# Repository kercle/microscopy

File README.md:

# Microscope automation project

This is a small passion project of mine in which I implement a few automations to my Bresser Researcher Trino 40-1000x. A few design-goals are:

- Minimally intrusive in the sense that the changes to the microscope should be revertible as much as possible.
- The microscope should still be fully usable in the original (analogue) way.

## Gallery

A few composite images obtained by focus stacking:

| Daphnia | Spider mite | Unknown mite |
|---------|-------------|--------------------------|
|  |  |  |
| *Notes:* The sample was treated with bleach in order to immobilize organisms. Brownian motion was prevented by stabilizing the sample in Xanthan gum. | *Notes:* The sample was frozen to immobilize the specimen. It was taken from one of my house plants. | *Notes:* The sample was collected from the soil in one of my house plants. It was immobilized by freezing. Possibly of the order Mesostigmata. |

## Hardware

### Electronics

The control electronics is split between two controllers. The low-level control is handled by an ESP32 microcontroller, with the stepping motors being driven by TMC2208 stepper drivers.

The high-level control is handled by a Raspberry Pi 4, however the housing also allows for the installation of a Jetson Nano device instead of the Raspberry Pi.

The Raspberry Pi and ESP32 communicate over a serial connection (UART) using a custom protocol.

## Software

### User interface and backend

The user interface is a web application served by the Raspberry Pi. The frontend is built using Svelte, Tailwind CSS and DaisyUI. The backend is a Rust application using the Axum framework.

### Firmware

The ESP32 firmware is written in Rust using the `esp-idf` framework and embassy.

## Roadmap / Ideas for future work

- [x] Motorized z-axis with endstops for focusing
- [x] Web interface for controlling the microscope
- [x] Live view from camera with controls for exposure, gain, white balance, etc.
- [x] Z-stack acquisition
- [ ] Build custom focus knob which interacts with the microcontroller to allow for manual focusing when not using the web interface.
- [ ] Motorized stage for x/y movement
- [ ] Build custom stage knobs which interact with the microcontroller to allow for manual x/y
- [ ] Objective turret slot detection
- [ ] Substage illumination control
- [ ] Incident illumination

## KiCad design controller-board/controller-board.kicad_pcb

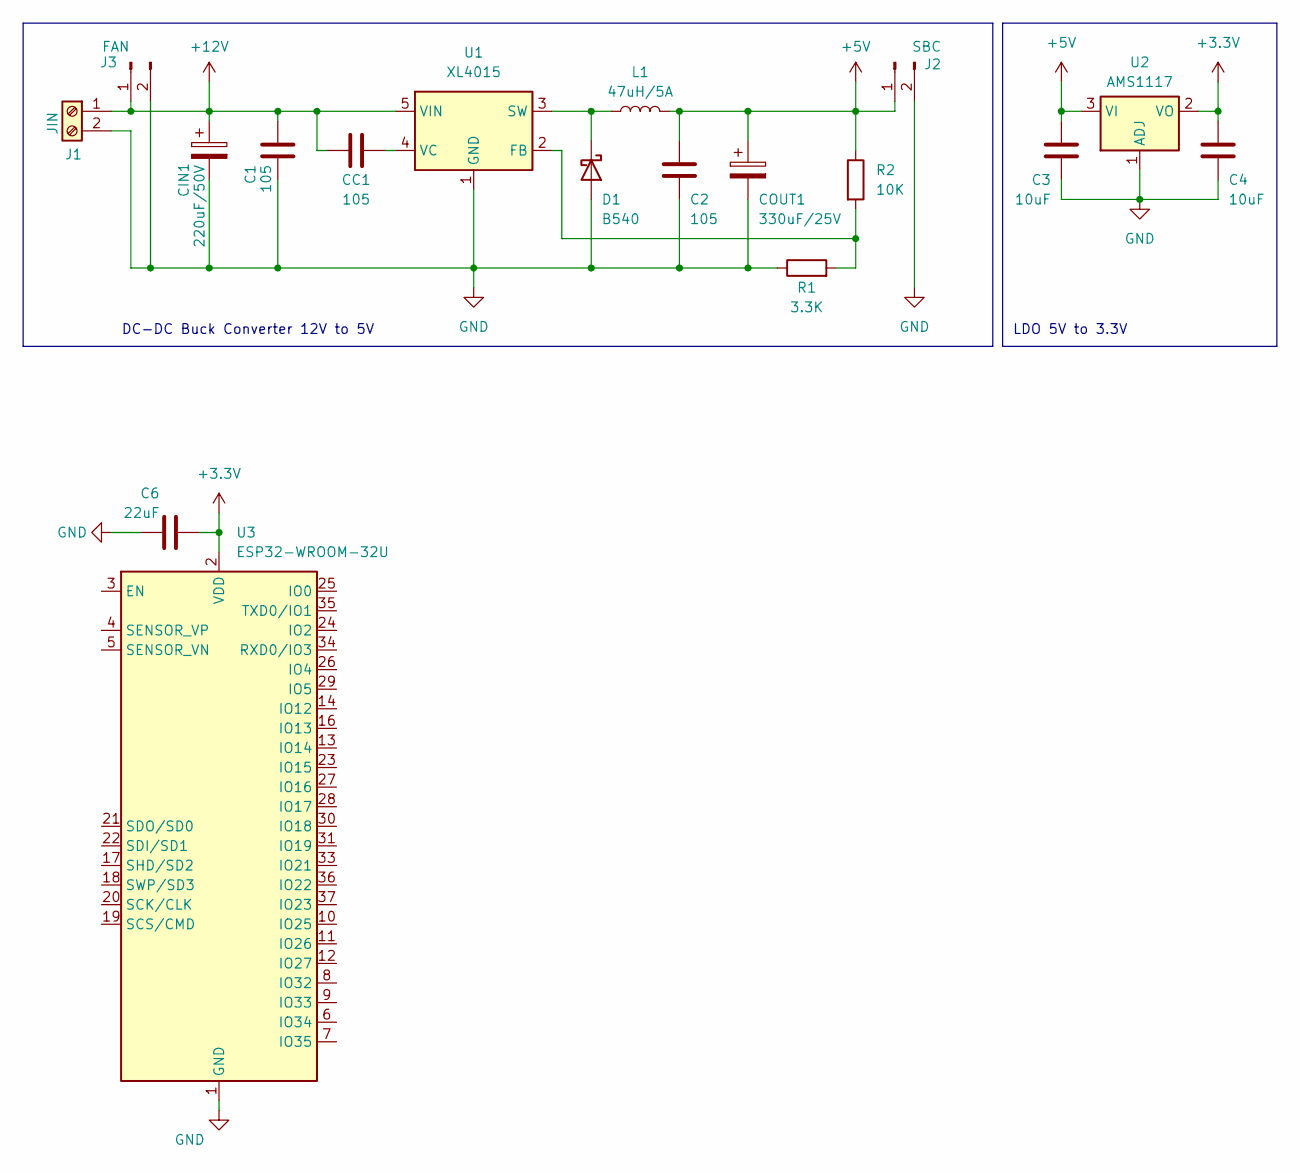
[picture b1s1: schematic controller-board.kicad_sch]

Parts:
C1, C2: 105; C_0805_2012Metric
C3, C4: 10uF; C_0805_2012Metric
C6: 22uF; C_0805_2012Metric
CC1: 105; C_0805_2012Metric
CIN1: 220uF/50V; CP_Elec_10x10; MFR# RVT1H221M1010 220UF 50V
COUT1: 330uF/25V; CP_Elec_10x10; MFR# RVT1H221M1010 220UF 50V
D1: B540; D_SMA
J1: JIN; TerminalBlock_Altech_AK300-2_P5.00mm
J2: SBC; JST_VH_B2P-VH-FB-B_1x02_P3.96mm_Vertical
J3: FAN; JST_VH_B2P-VH-FB-B_1x02_P3.96mm_Vertical
L1: 47uH/5A; L_Chilisin_BMRF00131360; MFR# YSPI1365-470M; JLCPCB# C497913
R1: 3.3K; R_0805_2012Metric
R2: 10K; R_0805_2012Metric
U1: XL4015; TO-263-5_TabPin3
U2: AMS1117; SOT-223-3_TabPin2
U3: ESP32-WROOM-32U

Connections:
+3.3V: C4.1, C6.2, U2.2 (VO), U3.2 (VDD)
+5V: C2.1, C3.1, COUT1.1, J2.1, L1.2, R2.1, U2.3 (VI)
+12V: C1.1, CC1.1, CIN1.1, J1.1, J3.1, U1.5 (VIN)
GND: C1.2, C2.2, C3.2, C4.2, C6.1, CIN1.2, COUT1.2, D1.2 (A), J1.2, J2.2, J3.2, R1.1, U1.1 (GND), U2.1 (ADJ), U3.1 (GND), U3.15 (GND), U3.38 (GND), U3.39 (GND)
unnamed: D1.1 (K), L1.1, U1.3 (SW)
unnamed: R1.2, R2.2, U1.2 (FB)
unnamed: CC1.2, U1.4 (VC)

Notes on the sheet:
DC-DC Buck Converter 12V to 5V
LDO 5V to 3.3V

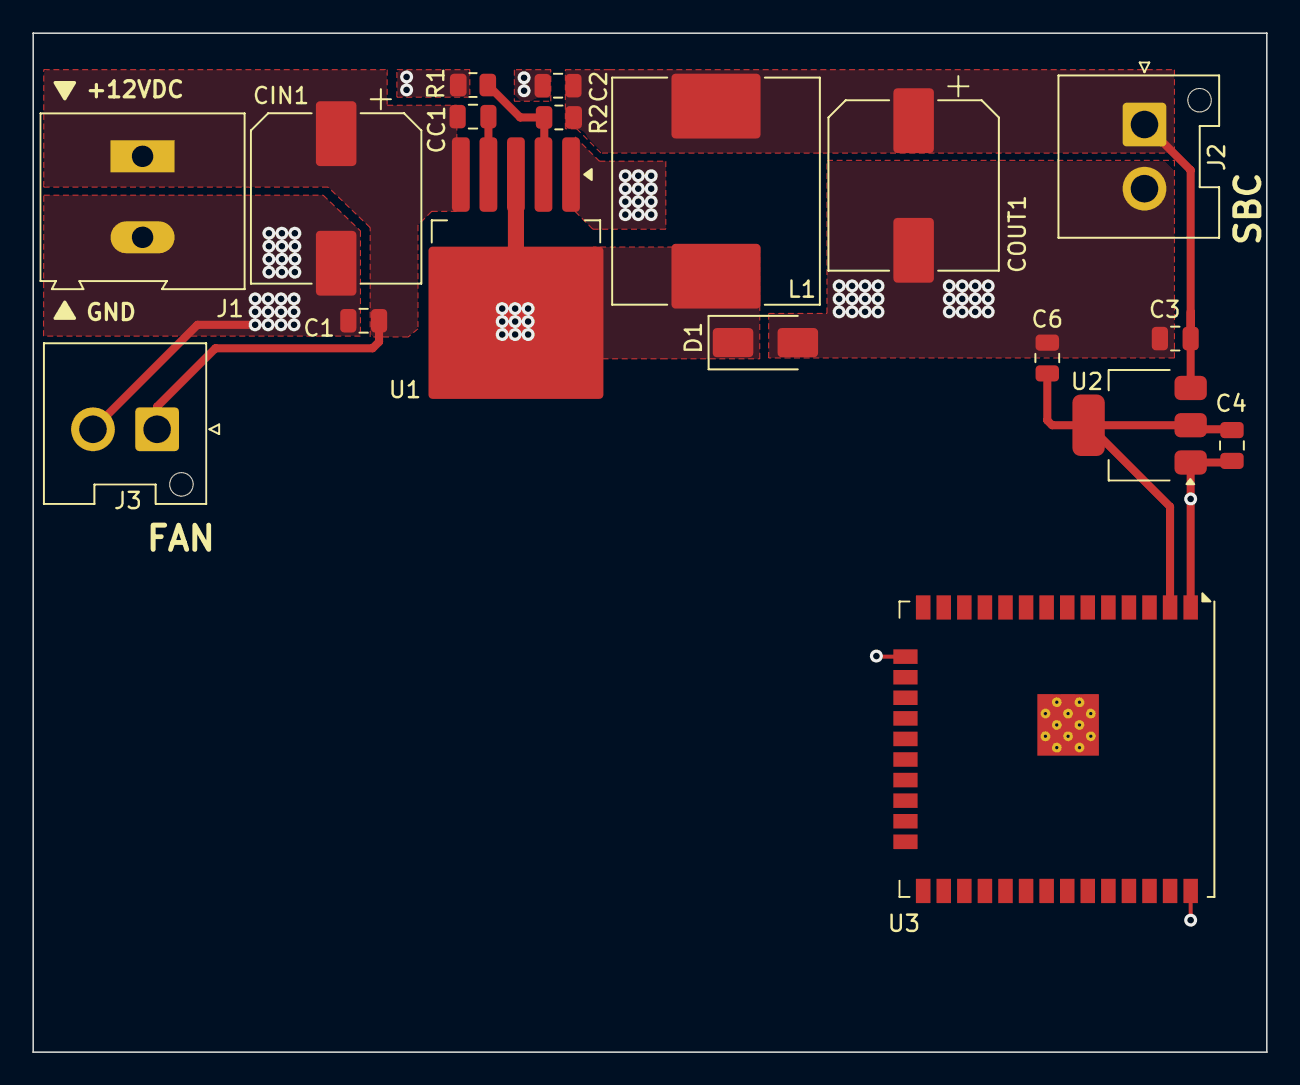
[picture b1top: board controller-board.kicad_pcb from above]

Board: 2 copper layers, 76.2 x 62.9 mm, 18 parts (0 on the bottom side), 7 nets.

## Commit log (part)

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2024-06-29 Initial Svelte app
2024-06-29 Add shadcn-svelte
2025-09-05 Starting designing the controller board.
2025-09-05 Get control app going.
2025-09-05 Ignore Kicad backups.
2025-09-07 Simple Axum-based HTTP server for serving MJPEG streams.
2025-09-07 Connect gstreamer to MJPEG stream.
2025-09-07 Make gstreamer source properties configurable.
2025-09-08 Connect MJPEG stream to gstreamer camera.
2025-09-08 experimenting with gst pipeline params.
2025-09-08 Delegate configuration away from initial pipeline.
2025-09-08 Use turbojpeg for better image quality.
2025-09-08 Simplify pipeline generation and dial down buffer size.
2025-09-08 Move backend into dedicated backend folder.
2025-09-08 Initialize clean svelte project.
2025-09-08 Serve and embed the frontend into binary.
2025-09-08 Simplify cross-build Dockerfile.
2025-09-08 Increase frame size a bit.
2025-09-08 Introdce WebSocket communication between client and server.
2025-09-08 Work on web-socket interaction between frontend and backend.
2025-09-08 Implementation of interactivity: exposure and test patterns.
2025-09-08 Better styling of UI
2025-09-08 Add contrast and saturation.
2025-09-09 Implement self-update capability and clean up frontend.
2025-09-09 Add auto white balance toggle and mode select.
2025-09-09 Fix default parameters.
2025-09-09 Add drawer icon.
2025-09-09 Add new controls: Color gains.
2025-09-09 Add tabs for differnet views.
2025-09-09 Record log messages to send them to the frontend.
2025-09-09 Send accumualated log messages on client connecting.
2025-09-09 Periodically send new logs to connected clients.
2025-09-10 Show logs on journal tab in frontend.
2025-09-10 Fix default parameters on pipeline startup.
2025-09-17 Add endpoint for taking high-resolution photos.
2025-09-18 Add a button to download hi-res photos.
2025-09-18 Adjust journal font.
2025-09-20 Initialize firmware template.
2025-09-20 Toggle of GPIO2 and printing 'Hello World!' from Esp32.
2025-09-21 Testing stage z-axis motor.
2025-09-21 Move all software into dedicated software folder.
2025-09-21 Add recipe for flashing esp32.
2025-09-21 Move service file into backend folder.
2025-09-21 Initialize library for communicaton between µC and SBC.
2025-09-21 Remove std bindings from com lib.
2025-09-21 Remove prints from firmware and link against com lib.
2025-09-21 Install embassy packages in firmware.
2025-09-21 Use embassy for firmware.
2025-09-21 Simplify firmware file hierarchy and fix rust warnings.
2025-09-21 WIP: Uart communication.
2025-09-21 Rename test binary for talking to the firmware to client to make the role clear.
2025-09-21 Set up UART to communicate with SBC.
2025-09-22 Have dedicated channels for each task.
2025-09-22 Add basic TUI for the client app based on the user input example of ratatui.
2025-09-22 Add command parsing using regex.
2025-09-22 Implement encoding and decoding messages.
2025-09-22 Refactoring client to work with tokio.
2025-09-22 Sync via serial port.
2025-09-22 Decode an print device events.
2025-09-22 Cleaning up and linting.
2025-09-22 Add quality of life feature to client: input history.
2025-09-22 Implement a driver for the serial port for easy integration.
2025-09-22 Cleaner error handling in CLI tool.
2025-09-22 Add function for resetting the device.
2025-09-23 Use new serial interface.
2025-09-23 Fancier printing of events.
2025-09-23 Linting.
2025-09-23 Add an entry to the justfile for manually interacting with the firmware via the serial port.
2025-09-23 Add communication dependency for backend.
2025-09-23 Refactor command parsing for easier extentiability.
2025-09-23 Add stage motor stop command.
2025-09-23 Implement stage motor stop command in firmware.
2025-09-23 Adding more commands for the stage motor.
2025-09-23 Create dedicated module for stage motor in firmware code and add more commands.
2025-09-23 Let the backend connect to the controller board via the serial port.
2025-09-23 Add REST endpoints for motor controller.
2025-09-26 Add more buttons for controlling the zStage from the frontend.
2025-09-26 Implement homing mechanic in firmware.
2025-09-26 Allow for setting lower limit to a specific step count.
2025-09-26 Add homing feature to backend and frontend.
2025-09-26 Allow for two different movement speeds.
2025-10-03 Use heapless's own format instead of assembling log message using push_str and automatically home when firmware starts.
2025-10-03 Rearrange match statement in motor_task.
2025-10-28 Add a semaphore to AppState in order to guard certain actions which are mutually exclusive, like taking photos and scanning a sample.
2025-10-28 Outsource creating a photo-pipeline to a separate function.
2025-10-28 Add a function to move the stage.
2025-10-28 Add a reusable function to take a photo and convert it to a bytes buffer.
2025-10-28 Add a backend API endpoint for starting a z_scan sequence.
2025-10-28 Storing z-scan images to a temporary folder.
2025-10-28 Wrap logic of z_scan in a nested exec function to reduce complexity.
2025-10-28 Linting backend implementation.
2025-10-29 Implement mechanism for cancelling operations.
2025-10-29 Allow for bi-directional z-scans and configurable directory for storing z-scan frames together with metadata.
2025-10-29 Endpoint for listing Z-Scans
2025-10-30 Endpoint for downloading thumbnails of z scans.
2025-10-30 New tab on frontend for scans.
2025-10-30 Draft sample scan control page.
2025-10-30 Refine sample scan control page.
2025-10-31 Connect sample scan page frontend to backend.
2025-10-31 Fix bookworm container.
2025-10-31 Caching thumbnails of zscans.
2025-10-31 Make image non-draggable.
2025-10-31 Fine-tune GUI.
2025-10-31 Implement ability to delete z scans.
2025-11-01 Make backend host configurable for development purposes.
2025-11-01 Move implemenation of REST endpoints into dedicated folder.
2025-11-01 Rename REST endpoint handlers for a cleaner code structure.
2025-11-01 Clean up old z_scan endpoints and reorganize CLI interface.
2025-11-01 Simplify handlers by moving command line arguments into AppState.
2025-11-01 In the Z-Scan thumbnails, use the middle frame in the list.
2025-11-01 Introduce a dedicated module for each CLI command.
2025-11-01 Added a bit of documentation and CAD models.
2025-11-01 Setup python environment and library for microscopy data exploration and experimentation.
2025-11-01 Getting started with fetching ZScans thumbnails in python library.
2025-11-01 Add OpenCV dependencies.
2025-11-02 Implement rudimentary focus stacking algorithm.
2025-11-02 Add endpoint for downloading full-size frames from z-scans.
2025-11-02 Process image stacks as memmapped arrays, since the images can get quite large.
2025-11-02 Move CAD data into hardware folder.
2025-11-03 Ignore all *_playground folders in software.
2025-11-13 Fix updating preview image if data array is empty.
2025-11-13 Adding processing tab for controlling processing nodes.
2025-11-13 Change pattern in dev environment to gradient.
2025-11-14 Populate first datastructures for centralizing web-socket protocol specification.
2025-11-14 Refactor CameraProperties and Parameters.
    The two structs are moved to the communication crate in order to unify the interface between the different components.
2025-11-14 Rename crate communication to interface.
2025-11-14 Hide ts-rs behind a dedicated feature since it does not play nicely with cross-compilation.
2025-11-14 Fix ttyUSB naming ambiguity by adding udev rules and refering to the respective unique ID.
2025-11-14 Bundle AppState and WebSocket object in a dedicated struct.
2025-11-14 Add a new field for differentiating between different peer roles.
2025-11-14 Use axum ws module in preamble.
2025-11-14 Bundle connection data into WsConnection struct.
2025-11-14 Add dedicated function to process text payloads received via web socket.
2025-11-14 Import WebSocketMessage directly.
2025-11-14 Parse web socket text payload in process_message function and pass result on to process_parsed_message.
2025-11-14 Allow for different client roles (UserClient, ComputeNode) in order to deligate processing tasks to different servers.
2025-11-14 Implement initial mechanism for registering compute nodes.
2025-11-14 Cleanup registering and unregistering compute nodes and broadcast list of compute nodes to user clients.
2025-11-14 Add input and output capabilities to compute nodes.
2025-11-14 Allow for display names and different procedures in compute nodes.
2025-11-14 Implement compute node skeleton.
2025-11-14 Announce compute nodes to new clients connecting to backend.
2025-11-15 Sketch code for rendering UI for compute node's procedures.
2025-11-17 Adjust processing UI elements.
2025-11-18 Implement concept for bi-directional communication between clients and compute nodes.
2025-11-18 Make FocusStacking client agnostic again.
2025-11-18 Track procedure ID and compute node ID in frontend for compute nodes.
2025-11-18 Add image preview for procedure inputs.
2025-11-18 Show preview of Z-Scan in procedure tab of the focus stacking procedure.
2025-11-18 In frontend, pass websocket connection to ProcedureInputs component to dynamically adjust inputs based on selection.
2025-11-19 Use url anchors to keep on the respectively selected tab when refreshing page.
2025-11-26 Added a bit of documentation for the hardware side-of-things.
2025-11-26 Rename interface crate to common crate for clearer terminology.
2025-11-27 Allow more flexible UI layout for compute nodes.
2025-11-27 Cleanup and register onChange function for select.
2025-11-28 Send parameters to compute node to receive new UI.
2025-11-28 Allow for slider elements in procedure UI.
2025-11-28 WIP: Update GUI based on response from compute node.
2025-11-28 Update procedure elements based on the compute node response.
2025-11-28 Update naming of structs to make the purpose better to understand.
2025-11-28 Split up describe function of focus stacking procedure.
2025-11-28 Move focus stacking module into folder.
2025-11-29 Make a central AppState for compute nodes that holds all the available procedures.
2025-11-29 Rename Procedure to Tasks for a cleaner terminology and less ambiguity.
2025-11-29 Fix minor issues from renaming procedures to tasks and print mock process to test signal chain.
2025-11-29 Make tasks in the compute node application more flexible for easier extensibility.
2025-11-29 Relay progress of compute tasks to sender thread in compute nodes.
2025-11-29 Add todo note.
2025-11-29 Send a progress update to clients.
2025-11-29 Move playground sub-modules to where they belong.
2025-11-29 Update progress in UI.
2025-11-29 Allow for an arbitrary amount of tasks per compute node.
2025-11-29 Make tasks tab scrollable if tasks overflow viewport.
2025-11-29 Increase gap between tasks on tasks tab.
2025-11-29 Remove dummy task.
2025-11-29 Adjusted focus stacking UI.
2025-11-30 Prepopulate ui values datastructure with initial values.
2025-11-30 Move focus stacking algorithm implementation into dedicated submodule.
2025-11-30 Download frames from z-stack in focus stacking task.
2025-11-30 Rearrange the project structure.
2025-11-30 Initialize GPU image processor for compute node.
2025-11-30 Pass GPU image processor on to the task execution.
2025-12-01 Implement a test for the sobel filter.
2025-12-01 Finalize initial implementation of `GpuImageProcessor` with sobel filter.
2025-12-02 Apply sobel filter to recorded image stack in focus stacking.
2025-12-02 Add gaussian_hblur shader.
2025-12-02 Implement Gaussian VBlur shader.
2025-12-02 Use tracing library for logging.
2025-12-02 Remove Gaussian blur filter again.
2025-12-02 Add box-blur and gaussian-blur in horizontal/vertical directions.
2025-12-02 Implement more convenient way of chaining filters.
2025-12-02 Place GPU-related code into dedicated module.
2025-12-02 Decouple image decoding function from focus stacking task.
2025-12-02 Reduce kernel size and increase iterates.
2025-12-02 Assemble final image in focus stacking.
2025-12-02 Take color of highest focus score instead of linear weighted sum.
